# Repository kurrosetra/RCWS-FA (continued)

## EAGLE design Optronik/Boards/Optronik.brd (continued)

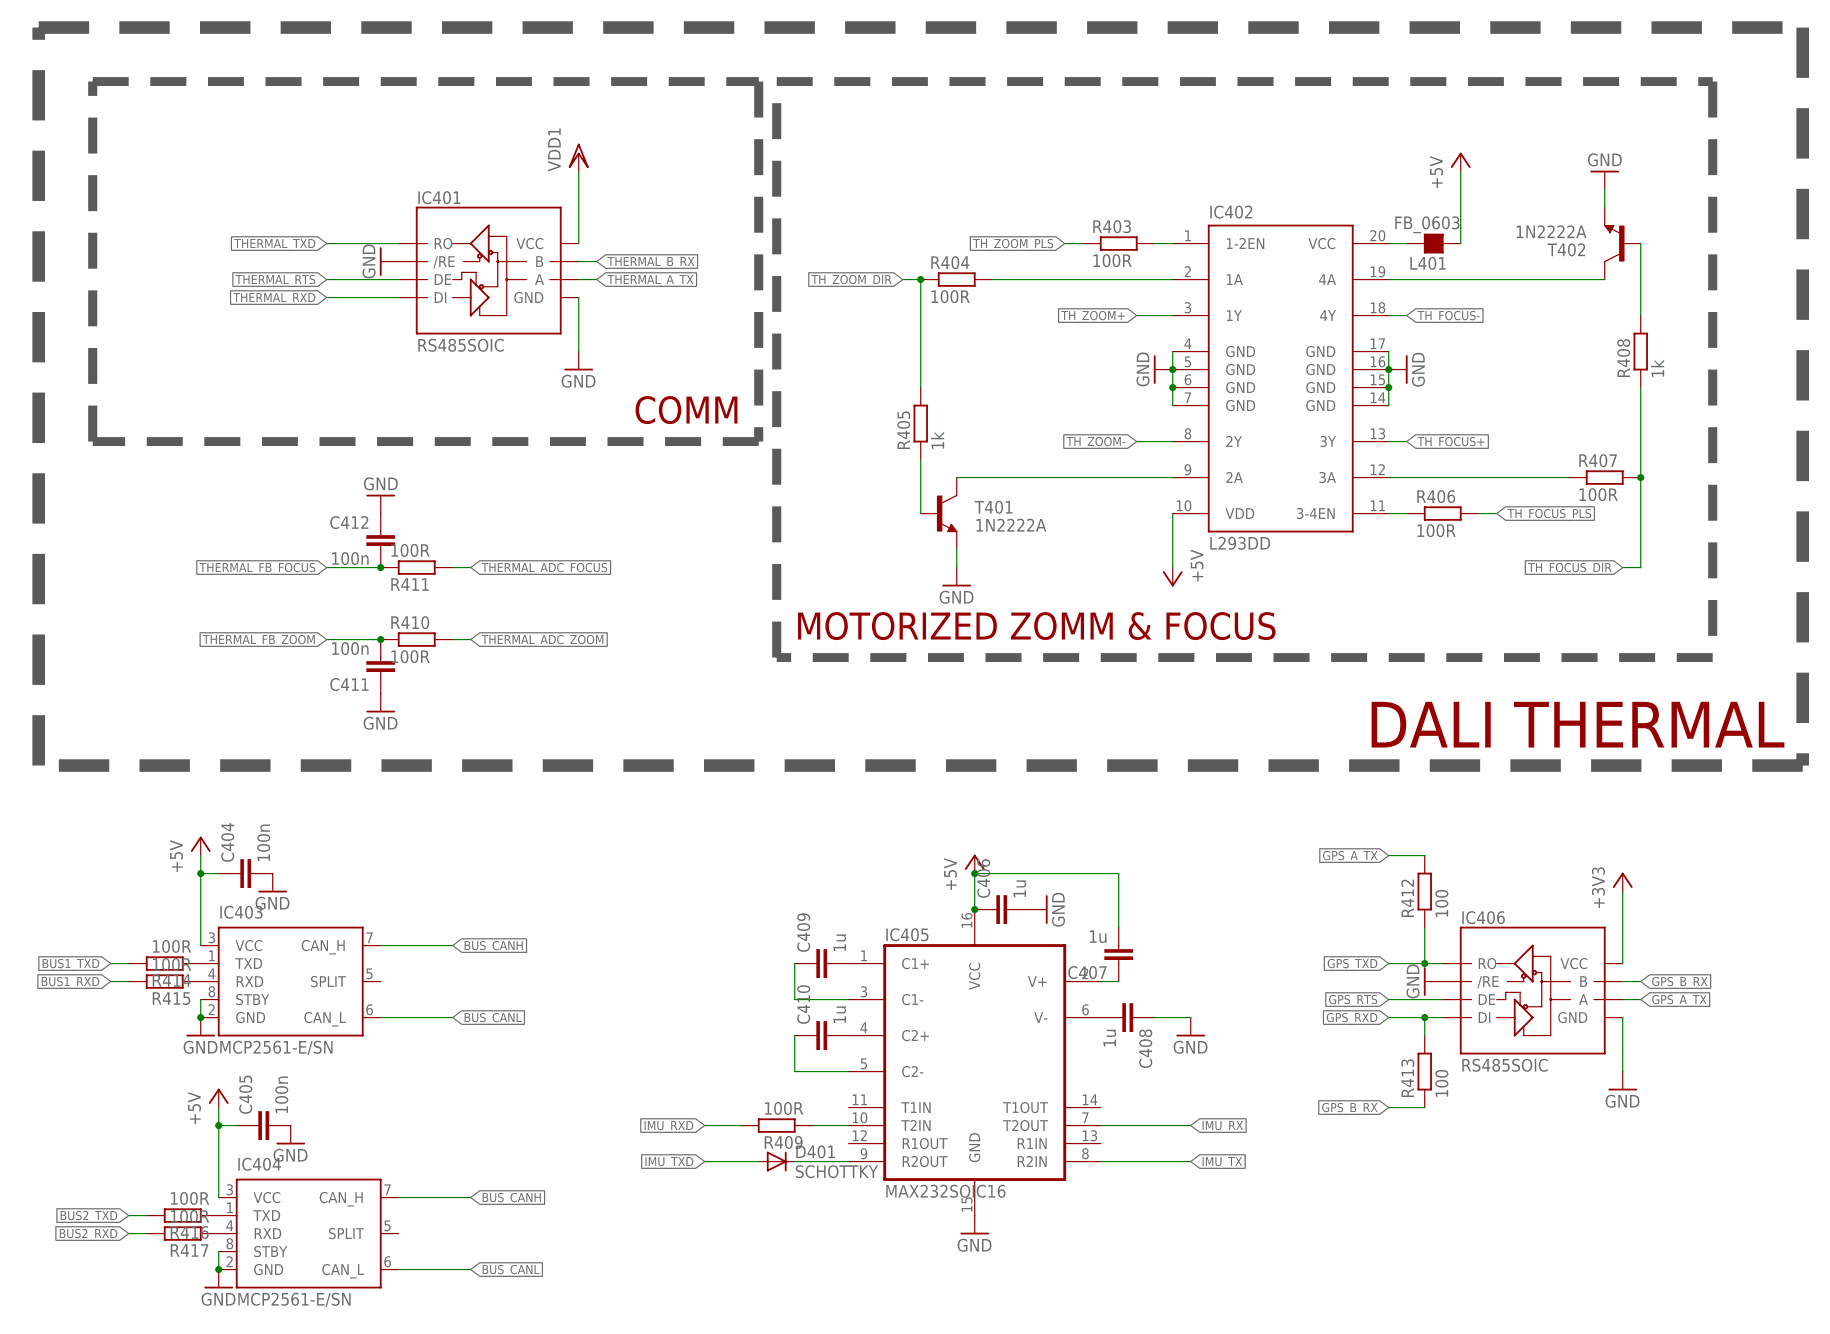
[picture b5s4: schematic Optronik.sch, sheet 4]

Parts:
C404, C405, C411, C412: 100n; C0603
C406, C407, C408, C409, C410: 1u; C0603
D401: SCHOTTKY; MICROMELF-W
IC401, IC406: RS485SOIC; SO08
IC402: L293DD; SO20W
IC403, IC404: MCP2561-E/SN; SOIC-8
IC405: MAX232SOIC16; SO016
L401: FB_0603; L0603
R403, R404, R406, R407, R409, R410, R411, R414, R415, R416, R417: 100R; R0603
R405, R408: 1k; R0603
R412, R413: 100; R0603
T401, T402: 1N2222A; SOT23

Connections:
+3V3: IC406.8 (VCC); also elsewhere on the board
+5V: C404.1, C405.1, C406.1, C407.2, IC402.10 (VDD), IC403.3 (VCC), IC404.3 (VCC), IC405.16 (VCC), L401.1; also elsewhere on the board
BUS1_RXD: R415.2; also elsewhere on the board
BUS1_TXD: R414.2; also elsewhere on the board
BUS2_RXD: R417.2; also elsewhere on the board
BUS2_TXD: R416.2; also elsewhere on the board
BUS_CANH: IC403.7 (CAN_H), IC404.7 (CAN_H); also elsewhere on the board
BUS_CANL: IC403.6 (CAN_L), IC404.6 (CAN_L); also elsewhere on the board
GND: C404.2, C405.2, C406.2, C408.1, C411.1, C412.1, IC401.2 (/RE), IC401.5 (GND), IC402.4 (GND), IC402.5 (GND), IC402.6 (GND), IC402.7 (GND), IC402.14 (GND), IC402.15 (GND), IC402.16 (GND), IC402.17 (GND), IC403.2 (GND), IC403.8 (STBY), IC404.2 (GND), IC404.8 (STBY), IC405.15 (GND), IC406.2 (/RE), IC406.5 (GND), T401.2 (E), T402.2 (E); also elsewhere on the board
GPS_A_TX: IC406.6 (A), R412.2; also elsewhere on the board
GPS_B_RX: IC406.7 (B), R413.1; also elsewhere on the board
GPS_RTS: IC406.3 (DE); also elsewhere on the board
GPS_RXD: IC406.4 (DI), R413.2; also elsewhere on the board
GPS_TXD: IC406.1 (RO), R412.1; also elsewhere on the board
IMU_RX: IC405.7 (T2OUT); also elsewhere on the board
IMU_RXD: R409.2; also elsewhere on the board
IMU_TX: IC405.8 (R2IN); also elsewhere on the board
IMU_TXD: D401.A; also elsewhere on the board
unnamed: IC402.20 (VCC), L401.2
unnamed: C408.2, IC405.6 (V-)
unnamed: C409.2, IC405.1 (C1+)
unnamed: C410.2, IC405.4 (C2+)
unnamed: IC402.12 (3A), R407.1
unnamed: IC403.1 (TXD), R414.1
unnamed: IC402.2 (1A), R404.2
unnamed: IC403.4 (RXD), R415.1
unnamed: C409.1, IC405.3 (C1-)
unnamed: C410.1, IC405.5 (C2-)
unnamed: IC404.1 (TXD), R416.1
unnamed: C407.1, IC405.2 (V+)
unnamed: IC404.4 (RXD), R417.1
unnamed: IC405.10 (T2IN), R409.1
unnamed: D401.C, IC405.9 (R2OUT)
unnamed: IC402.1 (1-2EN), R403.2
unnamed: IC402.11 (3-4EN), R406.1
unnamed: R405.1, T401.1 (B)
unnamed: IC402.9 (2A), T401.3 (C)
unnamed: IC402.19 (4A), T402.3 (C)
unnamed: R408.2, T402.1 (B)
THERMAL_ADC_FOCUS: R411.2; also elsewhere on the board
THERMAL_ADC_ZOOM: R410.2; also elsewhere on the board
THERMAL_A_TX: IC401.6 (A); also elsewhere on the board
THERMAL_B_RX: IC401.7 (B); also elsewhere on the board
THERMAL_FB_FOCUS: C412.2, R411.1; also elsewhere on the board
THERMAL_FB_ZOOM: C411.2, R410.1; also elsewhere on the board
THERMAL_RTS: IC401.3 (DE); also elsewhere on the board
THERMAL_RXD: IC401.4 (DI); also elsewhere on the board
THERMAL_TXD: IC401.1 (RO); also elsewhere on the board
TH_FOCUS+: IC402.13 (3Y); also elsewhere on the board
TH_FOCUS-: IC402.18 (4Y); also elsewhere on the board
TH_FOCUS_DIR: R407.2, R408.1; also elsewhere on the board
TH_FOCUS_PLS: R406.2; also elsewhere on the board
TH_ZOOM+: IC402.3 (1Y); also elsewhere on the board
TH_ZOOM-: IC402.8 (2Y); also elsewhere on the board
TH_ZOOM_DIR: R404.1, R405.2; also elsewhere on the board
TH_ZOOM_PLS: R403.1; also elsewhere on the board
VDD1: IC401.8 (VCC); also elsewhere on the board

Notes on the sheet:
DALI THERMAL
COMM
MOTORIZED ZOMM & FOCUS

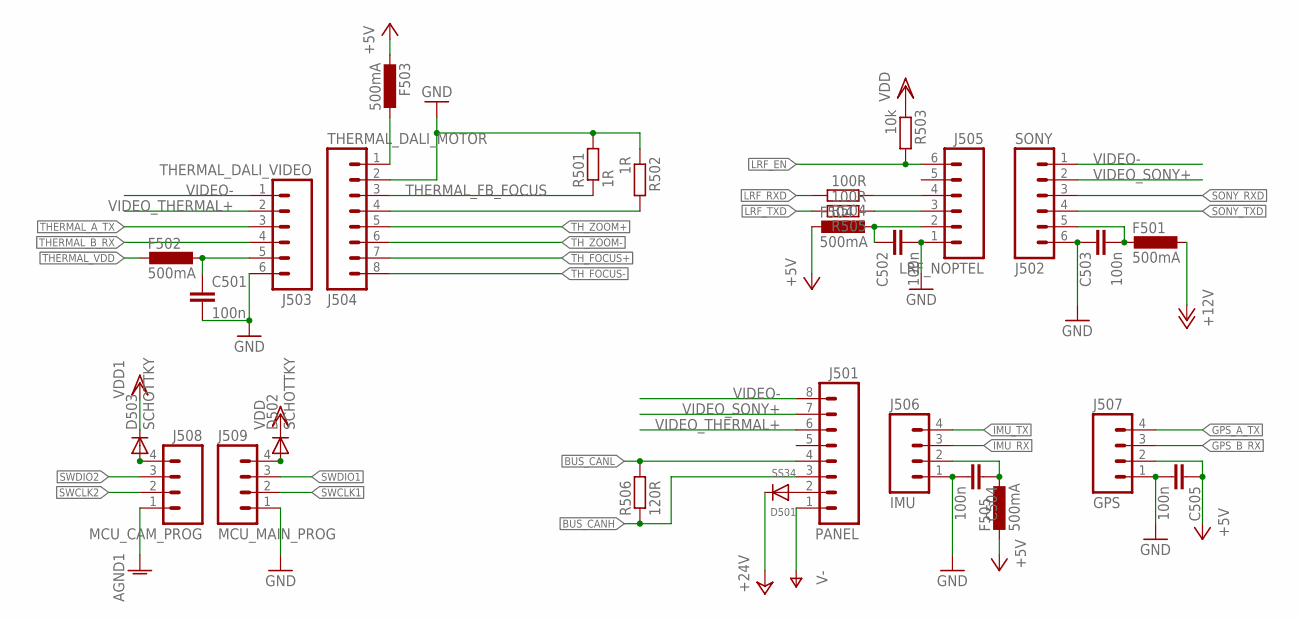
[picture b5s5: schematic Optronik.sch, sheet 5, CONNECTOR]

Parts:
C501, C502, C503, C504, C505: 100n; C0603
D501: SS34; SMADIODE
D502, D503: SCHOTTKY; MICROMELF-W
F501, F502, F503, F504, F505: 500mA; L0805
J501: PANEL; XH-8-RA
J502: SONY; XH-6-RA
J503: THERMAL_DALI_VIDEO; XH-6-RA
J504: THERMAL_DALI_MOTOR; XH-8-RA
J505: LRF_NOPTEL; XH-6-RA
J506: IMU; XH-4-RA
J507: GPS; XH-4-RA
J508: MCU_CAM_PROG; XH-4-VERT
J509: MCU_MAIN_PROG; XH-4-VERT
R501, R502: 1R; 0411V
R503: 10k; R0603
R504, R505: 100R; R0603
R506: 120R; R0603

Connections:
+5V: C505.1, F503.2, F504.2, F505.2, J507.2; also elsewhere on the board
+12V: F501.1; also elsewhere on the board
+24V: D501.C; also elsewhere on the board
AGND1: J508.1; also elsewhere on the board
BUS_CANH: J501.3, R506.1; also elsewhere on the board
BUS_CANL: J501.4, R506.2; also elsewhere on the board
GND: C501.2, C502.2, C503.1, C504.2, C505.2, J502.6, J503.6, J504.2, J505.1, J506.1, J507.1, J509.1, R501.2, R502.1; also elsewhere on the board
GPS_A_TX: J507.4; also elsewhere on the board
GPS_B_RX: J507.3; also elsewhere on the board
IMU_RX: J506.3; also elsewhere on the board
IMU_TX: J506.4; also elsewhere on the board
LRF_EN: J505.6, R503.2; also elsewhere on the board
LRF_RXD: R504.2; also elsewhere on the board
LRF_TXD: R505.2; also elsewhere on the board
unnamed: D501.A, J501.2
unnamed: F503.1, J504.1
unnamed: D502.A, J509.4
unnamed: C501.1, F502.1, J503.5
unnamed: C502.1, F504.1, J505.2
unnamed: C503.2, F501.2, J502.5
unnamed: C504.1, F505.1, J506.2
unnamed: J505.3, R505.1
unnamed: J505.4, R504.1
unnamed: D503.A, J508.4
SONY_RXD: J502.3; also elsewhere on the board
SONY_TXD: J502.4; also elsewhere on the board
SWCLK1: J509.2; also elsewhere on the board
SWCLK2: J508.2; also elsewhere on the board
SWDIO1: J509.3; also elsewhere on the board
SWDIO2: J508.3; also elsewhere on the board
THERMAL_A_TX: J503.3; also elsewhere on the board
THERMAL_B_RX: J503.4; also elsewhere on the board
THERMAL_FB_FOCUS: J504.3, R501.1; also elsewhere on the board
THERMAL_FB_ZOOM: J504.4, R502.2; also elsewhere on the board
THERMAL_VDD: F502.2; also elsewhere on the board
TH_FOCUS+: J504.7; also elsewhere on the board
TH_FOCUS-: J504.8; also elsewhere on the board
TH_ZOOM+: J504.5; also elsewhere on the board
TH_ZOOM-: J504.6; also elsewhere on the board
V-: J501.1; also elsewhere on the board
VDD: D502.C, R503.1; also elsewhere on the board
VDD1: D503.C; also elsewhere on the board
VIDEO-: J501.8, J502.1, J503.1
VIDEO_SONY+: J501.7, J502.2
VIDEO_THERMAL+: J501.6, J503.2

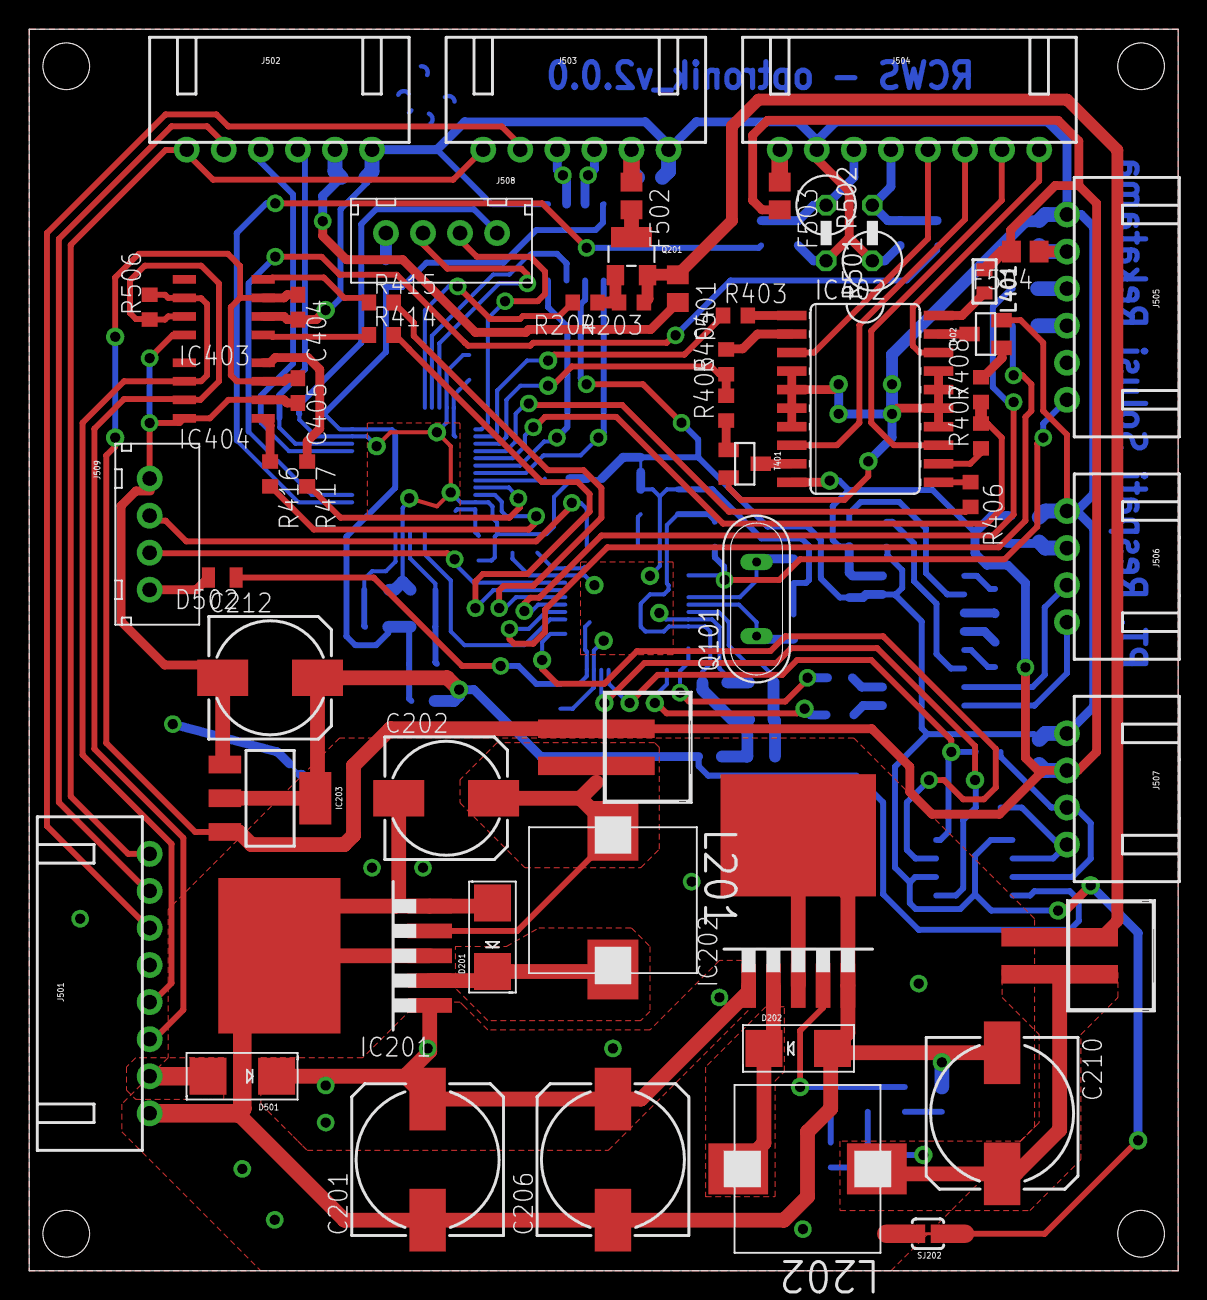
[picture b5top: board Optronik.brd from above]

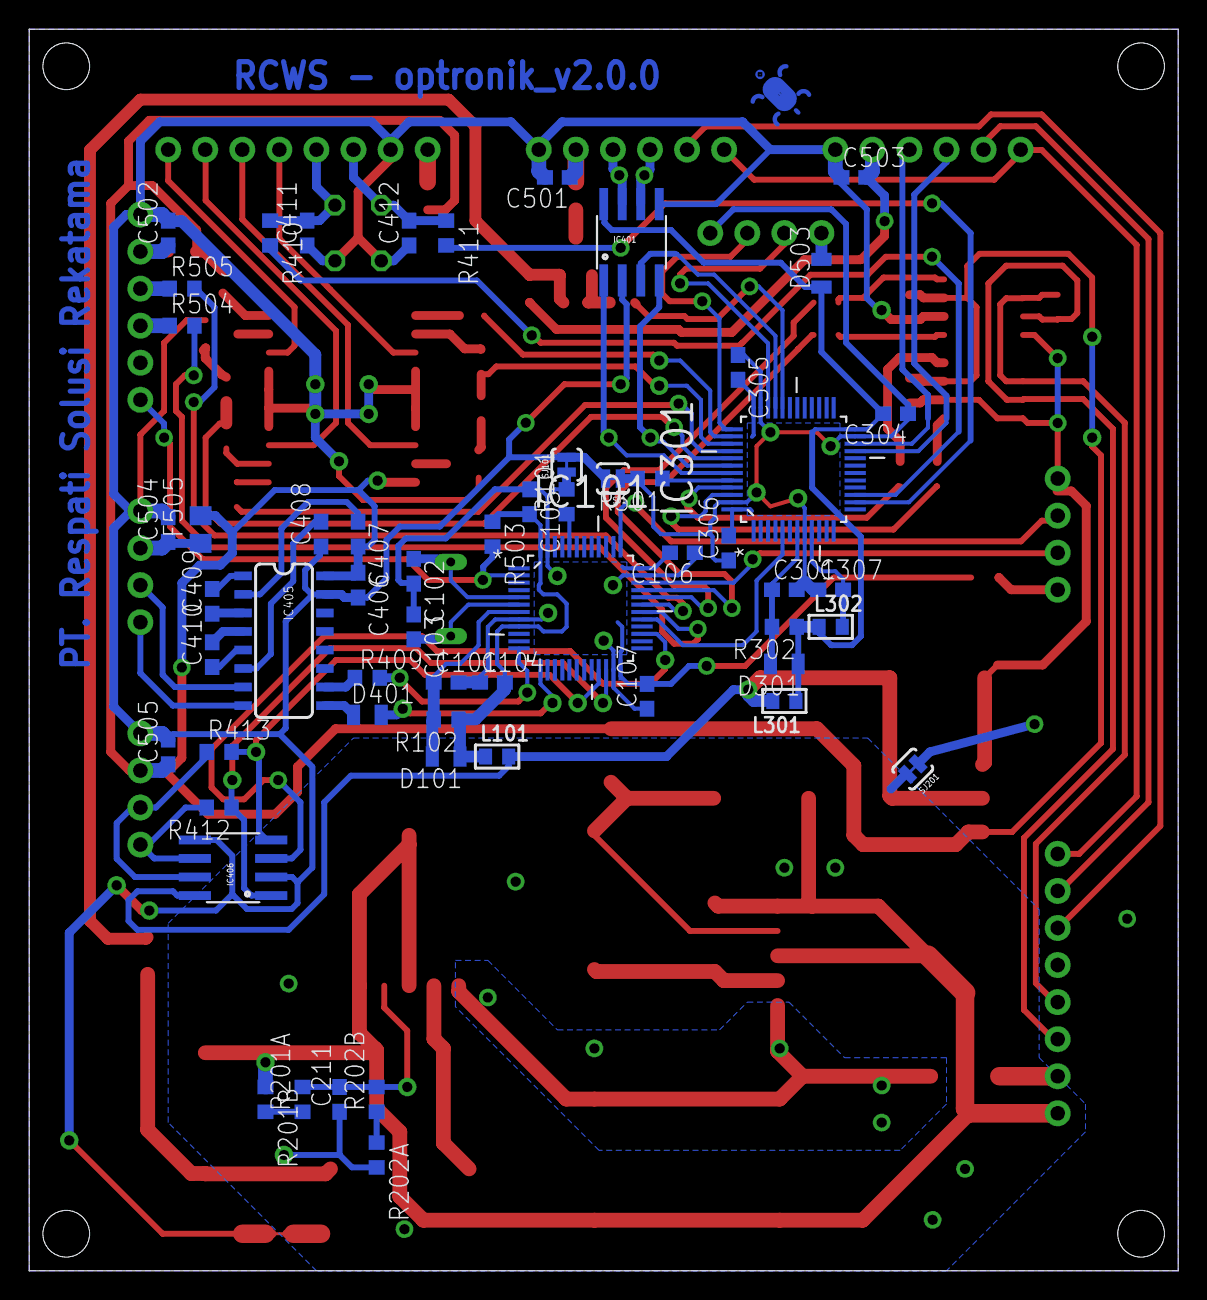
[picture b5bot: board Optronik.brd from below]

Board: 2 copper layers, 78.7 x 85.1 mm, 113 parts (57 on the bottom side), 103 nets.

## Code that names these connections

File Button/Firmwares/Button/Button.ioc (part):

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Mcu.Name=STM32F103C(8-B)Tx
Mcu.Package=LQFP48
Mcu.UserName=STM32F103C8Tx
PA0-WKUP.GPIOParameters=GPIO_PuPd,GPIO_Label
PA0-WKUP.GPIO_Label=TRK_ON
PA0-WKUP.GPIO_PuPd=GPIO_PULLUP
PA0-WKUP.Signal=GPIO_Input
PA1.GPIOParameters=GPIO_PuPd,GPIO_Label
PA1.GPIO_Label=FIRE_ACTIVE
PA1.GPIO_PuPd=GPIO_PULLUP
PA1.Signal=GPIO_Input
PA10.GPIOParameters=GPIO_PuPd,GPIO_Label
PA10.GPIO_Label=PANEL_TXD
PA10.GPIO_PuPd=GPIO_PULLUP
PA10.Mode=Asynchronous
PA10.Signal=USART1_RX
PA11.Signal=CAN_RX
PA12.Signal=CAN_TX
PA13.Mode=Serial_Wire
PA13.Signal=SYS_JTMS-SWDIO
PA14.Mode=Serial_Wire
PA14.Signal=SYS_JTCK-SWCLK
PA15.GPIOParameters=GPIO_PuPd,GPIO_Label,GPIO_Mode
PA15.GPIO_Label=CAM_ZOOM_OUT
PA15.GPIO_Mode=GPIO_MODE_INPUT
PA15.GPIO_PuPd=GPIO_PULLUP
PA15.Signal=GPIO_Input
PA2.GPIOParameters=GPIO_PuPd,GPIO_Label,GPIO_Mode
PA2.GPIO_Label=TRK_PREV
PA2.GPIO_Mode=GPIO_MODE_INPUT
PA2.GPIO_PuPd=GPIO_PULLUP
PA2.Signal=GPIO_Input
PA3.GPIOParameters=GPIO_PuPd,GPIO_Label,GPIO_Mode
PA3.GPIO_Label=CAM_FOCUS_NEAR
PA3.GPIO_Mode=GPIO_MODE_INPUT
PA3.GPIO_PuPd=GPIO_PULLUP
PA3.Signal=GPIO_Input
PA4.GPIOParameters=GPIO_PuPd,GPIO_Label,GPIO_Mode
PA4.GPIO_Label=CAM_SEL_THERMAL
PA4.GPIO_Mode=GPIO_MODE_INPUT
PA4.GPIO_PuPd=GPIO_PULLUP
PA4.Signal=GPIO_Input
PA5.GPIOParameters=GPIO_Label
PA5.GPIO_Label=JSL_ELEVATION
PA5.Signal=ADCx_IN5
PA6.GPIOParameters=GPIO_Label
PA6.GPIO_Label=JSL_AZIMUTH
PA6.Signal=ADCx_IN6
PA7.GPIOParameters=GPIO_PuPd,GPIO_Label,GPIO_Mode
PA7.GPIO_Label=JSR_DEADMAN
PA7.GPIO_Mode=GPIO_MODE_INPUT
PA7.GPIO_PuPd=GPIO_PULLUP
PA7.Signal=GPIO_Input
PA8.GPIOParameters=GPIO_PuPd,GPIO_Label,GPIO_Mode
PA8.GPIO_Label=JSL_TRIG
PA8.GPIO_Mode=GPIO_MODE_INPUT
PA8.GPIO_PuPd=GPIO_PULLUP
PA8.Signal=GPIO_Input
PA9.GPIOParameters=GPIO_Label
PA9.GPIO_Label=PANEL_RXD
PA9.Mode=Asynchronous
PA9.Signal=USART1_TX
PB0.GPIOParameters=GPIO_Label
PB0.GPIO_Label=JSR_AZIMUTH
PB0.Signal=ADCx_IN8
PB1.GPIOParameters=GPIO_Label
PB1.GPIO_Label=JSR_ELEVATION
PB1.Signal=ADCx_IN9
PB10.GPIOParameters=GPIO_PuPd,GPIO_Label,GPIO_Mode
PB10.GPIO_Label=JSR_B
PB10.GPIO_Mode=GPIO_MODE_INPUT
PB10.GPIO_PuPd=GPIO_PULLUP
PB10.Signal=GPIO_Input
PB11.GPIOParameters=GPIO_PuPd,GPIO_Label,GPIO_Mode
PB11.GPIO_Label=JSR_TRIG
PB11.GPIO_Mode=GPIO_MODE_INPUT
PB11.GPIO_PuPd=GPIO_PULLUP
PB11.Signal=GPIO_Input
PB12.GPIOParameters=PinState,GPIO_Label
PB12.GPIO_Label=LED
PB12.PinState=GPIO_PIN_SET
PB12.Signal=GPIO_Output
PB13.GPIOParameters=GPIO_PuPd,GPIO_Label,GPIO_Mode
PB13.GPIO_Label=JSL_DEADMAN
PB13.GPIO_Mode=GPIO_MODE_INPUT
PB13.GPIO_PuPd=GPIO_PULLUP
PB13.Signal=GPIO_Input
PB14.GPIOParameters=GPIO_PuPd,GPIO_Label,GPIO_Mode
PB14.GPIO_Label=JSL_A
PB14.GPIO_Mode=GPIO_MODE_INPUT
PB14.GPIO_PuPd=GPIO_PULLUP
PB14.Signal=GPIO_Input
PB15.GPIOParameters=GPIO_PuPd,GPIO_Label,GPIO_Mode
PB15.GPIO_Label=JSL_B
PB15.GPIO_Mode=GPIO_MODE_INPUT
PB15.GPIO_PuPd=GPIO_PULLUP
PB15.Signal=GPIO_Input
PB2.GPIOParameters=GPIO_PuPd,GPIO_Label,GPIO_Mode
PB2.GPIO_Label=JSR_A
PB2.GPIO_Mode=GPIO_MODE_INPUT
PB2.GPIO_PuPd=GPIO_PULLUP
PB2.Signal=GPIO_Input
PB3.GPIOParameters=GPIO_PuPd,GPIO_Label,GPIO_Mode
PB3.GPIO_Label=LRF_MAN_DOWN
PB3.GPIO_Mode=GPIO_MODE_INPUT
PB3.GPIO_PuPd=GPIO_PULLUP
PB3.Signal=GPIO_Input
PB4.GPIOParameters=GPIO_PuPd,GPIO_Label,GPIO_Mode
PB4.GPIO_Label=LRF_START
PB4.GPIO_Mode=GPIO_MODE_INPUT
PB4.GPIO_PuPd=GPIO_PULLUP
PB4.Signal=GPIO_Input
PB5.GPIOParameters=GPIO_PuPd,GPIO_Label,GPIO_Mode
PB5.GPIO_Label=MTR_SPD_HIGH
PB5.GPIO_Mode=GPIO_MODE_INPUT
PB5.GPIO_PuPd=GPIO_PULLUP
PB5.Signal=GPIO_Input
PB6.GPIOParameters=GPIO_PuPd,GPIO_Label,GPIO_Mode
PB6.GPIO_Label=MTR_SPD_LOW
PB6.GPIO_Mode=GPIO_MODE_INPUT
PB6.GPIO_PuPd=GPIO_PULLUP
PB6.Signal=GPIO_Input
PB7.GPIOParameters=GPIO_PuPd,GPIO_Label,GPIO_Mode
PB7.GPIO_Label=LRF_EN
PB7.GPIO_Mode=GPIO_MODE_INPUT
PB7.GPIO_PuPd=GPIO_PULLUP
PB7.Signal=GPIO_Input
PB8.GPIOParameters=GPIO_PuPd,GPIO_Label,GPIO_Mode
PB8.GPIO_Label=LRF_MAN_UP
PB8.GPIO_Mode=GPIO_MODE_INPUT
PB8.GPIO_PuPd=GPIO_PULLUP
PB8.Signal=GPIO_Input
PB9.GPIOParameters=GPIO_PuPd,GPIO_Label,GPIO_Mode
PB9.GPIO_Label=CAM_ZOOM_IN
PB9.GPIO_Mode=GPIO_MODE_INPUT
PB9.GPIO_PuPd=GPIO_PULLUP
PB9.Signal=GPIO_Input
PC13-TAMPER-RTC.GPIOParameters=GPIO_Label
PC13-TAMPER-RTC.GPIO_Label=LED1
PC13-TAMPER-RTC.Signal=GPIO_Output
PC14-OSC32_IN.GPIOParameters=GPIO_Label
PC14-OSC32_IN.GPIO_Label=LED2
PC14-OSC32_IN.Signal=GPIO_Output
PC15-OSC32_OUT.GPIOParameters=GPIO_PuPd,GPIO_Label,GPIO_Mode
PC15-OSC32_OUT.GPIO_Label=CAM_SEL_DAY
PC15-OSC32_OUT.GPIO_Mode=GPIO_MODE_INPUT
PC15-OSC32_OUT.GPIO_PuPd=GPIO_PULLUP
PC15-OSC32_OUT.Signal=GPIO_Input
PD0-OSC_IN.GPIOParameters=GPIO_PuPd,GPIO_Label,GPIO_Mode
PD0-OSC_IN.GPIO_Label=CAM_FOCUS_FAR
PD0-OSC_IN.GPIO_Mode=GPIO_MODE_INPUT
PD0-OSC_IN.GPIO_PuPd=GPIO_PULLUP
PD0-OSC_IN.Signal=GPIO_Input
PD1-OSC_OUT.GPIOParameters=GPIO_PuPd,GPIO_Label,GPIO_Mode
PD1-OSC_OUT.GPIO_Label=TRK_NEXT
PD1-OSC_OUT.GPIO_Mode=GPIO_MODE_INPUT
PD1-OSC_OUT.GPIO_PuPd=GPIO_PULLUP
PD1-OSC_OUT.Signal=GPIO_Input
RCC.SYSCLKFreq_VALUE=36000000
RCC.SYSCLKSource=RCC_SYSCLKSOURCE_PLLCLK
board=custom

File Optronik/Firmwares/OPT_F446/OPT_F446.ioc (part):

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Mcu.Name=STM32F446R(C-E)Tx
Mcu.Package=LQFP64
Mcu.UserName=STM32F446RETx
PA0-WKUP.GPIOParameters=GPIO_Label
PA0-WKUP.GPIO_Label=DEBUG_RXD
PA0-WKUP.Mode=Asynchronous
PA0-WKUP.Signal=UART4_TX
PA1.GPIOParameters=GPIO_Label
PA1.GPIO_Label=DEBUG_TXD
PA1.Mode=Asynchronous
PA1.Signal=UART4_RX
PA10.GPIOParameters=GPIO_Label
PA10.GPIO_Label=RESV_TXD
PA10.Signal=USART1_RX
PA11.Mode=CAN_Activate
PA11.Signal=CAN1_RX
PA12.Mode=CAN_Activate
PA12.Signal=CAN1_TX
PA13.GPIOParameters=GPIO_Label
PA13.GPIO_Label=TMS
PA13.Mode=Serial_Wire
PA13.Signal=SYS_JTMS-SWDIO
PA14.GPIOParameters=GPIO_Label
PA14.GPIO_Label=TCK
PA14.Mode=Serial_Wire
PA14.Signal=SYS_JTCK-SWCLK
PA15.GPIOParameters=GPIO_PuPd,GPIO_Label
PA15.GPIO_Label=THERMAL_PWR_EN
PA15.GPIO_PuPd=GPIO_PULLUP
PA15.Signal=GPIO_Output
PA2.GPIOParameters=GPIO_Label
PA2.GPIO_Label=LRF_RXD
PA2.Mode=Asynchronous
PA2.Signal=USART2_TX
PA3.GPIOParameters=GPIO_Label
PA3.GPIO_Label=LRF_TXD
PA3.Mode=Asynchronous
PA3.Signal=USART2_RX
PA4.Signal=GPIO_Input
PA5.Signal=GPIO_Input
PA6.GPIOParameters=GPIO_Speed,PinState,GPIO_PuPd,GPIO_Label
PA6.GPIO_Label=LRF_EN
PA6.GPIO_PuPd=GPIO_PULLUP
PA6.GPIO_Speed=GPIO_SPEED_FREQ_VERY_HIGH
PA6.PinState=GPIO_PIN_SET
PA6.Signal=GPIO_Output
PA7.Signal=GPIO_Input
PA9.GPIOParameters=GPIO_Label
PA9.GPIO_Label=RESV_RXD
PA9.Signal=USART1_TX
PB15.GPIOParameters=GPIO_PuPd,GPIO_Label
PB15.GPIO_Label=CAM_SELECT
PB15.GPIO_PuPd=GPIO_PULLUP
PB15.Signal=GPIO_Output
PB3.GPIOParameters=GPIO_Speed,GPIO_PuPd,GPIO_Label
PB3.GPIO_Label=THERMAL_DE
PB3.GPIO_PuPd=GPIO_PULLUP
PB3.GPIO_Speed=GPIO_SPEED_FREQ_VERY_HIGH
PB3.Signal=GPIO_Output
PB6.GPIOParameters=PinState,GPIO_PuPd,GPIO_Label
PB6.GPIO_Label=LED_BUILTIN
PB6.GPIO_PuPd=GPIO_PULLUP
PB6.PinState=GPIO_PIN_SET
PB6.Signal=GPIO_Output
PC10.GPIOParameters=GPIO_Label
PC10.GPIO_Label=THERMAL_RXD
PC10.Mode=Asynchronous
PC10.Signal=USART3_TX
PC11.GPIOParameters=GPIO_Label
PC11.GPIO_Label=THERMAL_TXD
PC11.Mode=Asynchronous
PC11.Signal=USART3_RX
PC12.GPIOParameters=GPIO_Label
PC12.GPIO_Label=IMU_RXD
PC12.Signal=UART5_TX
PC4.Signal=GPIO_Input
PC6.GPIOParameters=GPIO_Label
PC6.GPIO_Label=SONY_RXD
PC6.Mode=Asynchronous
PC6.Signal=USART6_TX
PC7.GPIOParameters=GPIO_Label
PC7.GPIO_Label=SONY_TXD
PC7.Mode=Asynchronous
PC7.Signal=USART6_RX
PD2.GPIOParameters=GPIO_Label
PD2.GPIO_Label=IMU_TXD
PD2.Signal=UART5_RX
PH0-OSC_IN.Mode=HSE-External-Oscillator
PH0-OSC_IN.Signal=RCC_OSC_IN
PH1-OSC_OUT.Mode=HSE-External-Oscillator
PH1-OSC_OUT.Signal=RCC_OSC_OUT
RCC.HSE_VALUE=8000000
RCC.SYSCLKFreq_VALUE=180000000
RCC.SYSCLKSource=RCC_SYSCLKSOURCE_PLLCLK
board=NUCLEO-F446RE
boardIOC=true

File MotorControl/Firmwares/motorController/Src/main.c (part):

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#endif	//if DEBUG==1

	if (motorInit() != HAL_OK) {
		HAL_GPIO_WritePin(LED_BUILTIN_GPIO_Port, LED_BUILTIN_Pin, GPIO_PIN_RESET);
		while (1)
			;
	}
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#endif	//if DEBUG==1

	if (busInit() != HAL_OK) {
		HAL_GPIO_WritePin(LED_BUILTIN_GPIO_Port, LED_BUILTIN_Pin, GPIO_PIN_RESET);
		while (1)
			;
	}
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	;

	/*Configure GPIO pin Output Level */
	HAL_GPIO_WritePin(LED_BUILTIN_GPIO_Port, LED_BUILTIN_Pin, GPIO_PIN_SET);

	/*Configure GPIO pin Output Level */
	HAL_GPIO_WritePin(TRIGGER_ENABLE_GPIO_Port, TRIGGER_ENABLE_Pin, GPIO_PIN_RESET);

	/*Configure GPIO pins : PC13 PC14 PC15 PC0
	 PC1 PC2 PC3 PC4
	 PC5 PC8 PC9 PC10
	 PC11 PC12 */
	GPIO_InitStruct.Pin = GPIO_PIN_13 | GPIO_PIN_14 | GPIO_PIN_15 | GPIO_PIN_0 | GPIO_PIN_1
			| GPIO_PIN_2 | GPIO_PIN_3 | GPIO_PIN_4 | GPIO_PIN_5 | GPIO_PIN_8 | GPIO_PIN_9
			| GPIO_PIN_10 | GPIO_PIN_11 | GPIO_PIN_12;
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	GPIO_InitStruct.Pull = GPIO_NOPULL;
	HAL_GPIO_Init(GPIOC, &GPIO_InitStruct);

	/*Configure GPIO pins : PA0 PA4 PA5 PA6
	 PA8 PA9 PA10 PA11
	 PA12 PA15 */
	GPIO_InitStruct.Pin = GPIO_PIN_0 | GPIO_PIN_4 | GPIO_PIN_5 | GPIO_PIN_6 | GPIO_PIN_8
			| GPIO_PIN_9 | GPIO_PIN_10 | GPIO_PIN_11 | GPIO_PIN_12 | GPIO_PIN_15;
	GPIO_InitStruct.Mode = GPIO_MODE_ANALOG;
	GPIO_InitStruct.Pull = GPIO_NOPULL;
	HAL_GPIO_Init(GPIOA, &GPIO_InitStruct);

	/*Configure GPIO pins : LIM_AZ_Pin LIM_EL_UP_Pin LIM_EL_DOWN_Pin */
	GPIO_InitStruct.Pin = LIM_AZ_Pin | LIM_EL_UP_Pin | LIM_EL_DOWN_Pin;
	GPIO_InitStruct.Mode = GPIO_MODE_IT_FALLING;
	GPIO_InitStruct.Pull = GPIO_PULLUP;
	HAL_GPIO_Init(GPIOA, &GPIO_InitStruct);

	/*Configure GPIO pin : LED_BUILTIN_Pin */
	GPIO_InitStruct.Pin = LED_BUILTIN_Pin;
	GPIO_InitStruct.Mode = GPIO_MODE_OUTPUT_PP;
	GPIO_InitStruct.Pull = GPIO_NOPULL;
	GPIO_InitStruct.Speed = GPIO_SPEED_FREQ_HIGH;
	HAL_GPIO_Init(LED_BUILTIN_GPIO_Port, &GPIO_InitStruct);

	/*Configure GPIO pins : PB0 PB1 PB2 PB10
	 PB14 PB15 PB3 PB5
	 PB6 PB7 */
	GPIO_InitStruct.Pin = GPIO_PIN_0 | GPIO_PIN_1 | GPIO_PIN_2 | GPIO_PIN_10 | GPIO_PIN_14
			| GPIO_PIN_15 | GPIO_PIN_3 | GPIO_PIN_5 | GPIO_PIN_6 | GPIO_PIN_7;
	GPIO_InitStruct.Mode = GPIO_MODE_ANALOG;
	GPIO_InitStruct.Pull = GPIO_NOPULL;
	HAL_GPIO_Init(GPIOB, &GPIO_InitStruct);

	/*Configure GPIO pin : PD2 */
	GPIO_InitStruct.Pin = GPIO_PIN_2;
	GPIO_InitStruct.Mode = GPIO_MODE_ANALOG;
	GPIO_InitStruct.Pull = GPIO_NOPULL;
	HAL_GPIO_Init(GPIOD, &GPIO_InitStruct);

	/*Configure GPIO pin : TRIGGER_ENABLE_Pin */
	GPIO_InitStruct.Pin = TRIGGER_ENABLE_Pin;
	GPIO_InitStruct.Mode = GPIO_MODE_OUTPUT_PP;
	GPIO_InitStruct.Pull = GPIO_PULLDOWN;
	GPIO_InitStruct.Speed = GPIO_SPEED_FREQ_HIGH;
	HAL_GPIO_Init(TRIGGER_ENABLE_GPIO_Port, &GPIO_InitStruct);

}

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
	/* check TRIGGER command */
	if (HAL_GetTick() >= buttonCommandTimeout) {
		HAL_GPIO_WritePin(TRIGGER_ENABLE_GPIO_Port, TRIGGER_ENABLE_Pin, GPIO_PIN_RESET);
		canRecvButton.online = false;
	}

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		buttonCommandTimeout = HAL_GetTick() + COMMAND_RECEIVE_TIMEOUT;
		canRecvButton.online = true;

		HAL_GPIO_WritePin(TRIGGER_ENABLE_GPIO_Port, TRIGGER_ENABLE_Pin,
				bitRead(canRecvButton.data[0], 0));

		cockStart = bitRead(canRecvButton.data[0], 1);
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	if (canRecvMoveMode.online) {
		/* check movement mode command (from panel) */
		if (HAL_GetTick() >= movementModeTimeout) {
			HAL_GPIO_WritePin(LED_BUILTIN_GPIO_Port, LED_BUILTIN_Pin, GPIO_PIN_RESET);
			canRecvMoveMode.online = false;
		}

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			initMovementState();
		}

		HAL_GPIO_TogglePin(LED_BUILTIN_GPIO_Port, LED_BUILTIN_Pin);
	}

}
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		_stateTimer = HAL_GetTick() + 100;

		bitWrite(canSendMotor.data[1], 0,
				HAL_GPIO_ReadPin(TRIGGER_ENABLE_GPIO_Port, TRIGGER_ENABLE_Pin));
		bitWrite(canSendMotor.data[1], 1, cockStart);

		busTxHeader->StdId = canSendMotor.id;
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
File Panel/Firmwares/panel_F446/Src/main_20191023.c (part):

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typedef enum
{
	MTR_SPD_MID = 2,
	MTR_SPD_LOW = 0,
	MTR_SPD_HIGH = 3
} MotorSpeed_e;

const uint32_t MTR_PAN_SPEED_JOYSTICK_MAX = 100000;
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	HAL_IWDG_Init(&hiwdg);
	HAL_IWDG_Refresh(&hiwdg);

	HAL_GPIO_WritePin(LED_BUILTIN_GPIO_Port, LED_BUILTIN_Pin, GPIO_PIN_SET);

#if DEBUG
	serial_init(&debug);
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
			bufLen = sprintf(buf, "%sBattVolt= %dmV", vt100_lineX[2], battVoltActual(battVolt));
			serial_write_str(&debug, buf, bufLen);
			HAL_GPIO_TogglePin(LED_BUILTIN_GPIO_Port, LED_BUILTIN_Pin);
		}
#endif	//if DEBUG==1

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 * EXTI
 * Free pins are configured automatically as Analog (this feature is enabled through
 * the Code Generation settings)
 PC6   ------> USART6_TX
 PC7   ------> USART6_RX
 PC10   ------> UART4_TX
 PC11   ------> UART4_RX
 */
static void MX_GPIO_Init(void)
{
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	;

	/*Configure GPIO pin Output Level */
	HAL_GPIO_WritePin(GPIOC, PC_IGNITION_Pin | WIFI_RST_Pin, GPIO_PIN_RESET);

	/*Configure GPIO pin Output Level */
	HAL_GPIO_WritePin(WIFI_EN_GPIO_Port, WIFI_EN_Pin, GPIO_PIN_RESET);

	/*Configure GPIO pin Output Level */
	HAL_GPIO_WritePin(LED_BUILTIN_GPIO_Port, LED_BUILTIN_Pin, GPIO_PIN_RESET);

	/*Configure GPIO pins : PC13 PC14 PC15 PC0
	 PC1 PC2 PC3 PC4 */
	GPIO_InitStruct.Pin = GPIO_PIN_13 | GPIO_PIN_14 | GPIO_PIN_15 | GPIO_PIN_0 | GPIO_PIN_1
			| GPIO_PIN_2 | GPIO_PIN_3 | GPIO_PIN_4;
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	GPIO_InitStruct.Pull = GPIO_NOPULL;
	HAL_GPIO_Init(GPIOC, &GPIO_InitStruct);

	/*Configure GPIO pins : PA0 PA1 PA4 PA5
	 PA6 PA8 */
	GPIO_InitStruct.Pin = GPIO_PIN_0 | GPIO_PIN_1 | GPIO_PIN_4 | GPIO_PIN_5 | GPIO_PIN_6
			| GPIO_PIN_8;
	GPIO_InitStruct.Mode = GPIO_MODE_ANALOG;
	GPIO_InitStruct.Pull = GPIO_NOPULL;
	HAL_GPIO_Init(GPIOA, &GPIO_InitStruct);

	/*Configure GPIO pins : PB0 PB1 PB2 PB13
	 PB14 PB3 PB4 PB5
	 PB6 PB7 PB8 PB9 */
	GPIO_InitStruct.Pin = GPIO_PIN_0 | GPIO_PIN_1 | GPIO_PIN_2 | GPIO_PIN_13 | GPIO_PIN_14
			| GPIO_PIN_3 | GPIO_PIN_4 | GPIO_PIN_5 | GPIO_PIN_6 | GPIO_PIN_7 | GPIO_PIN_8
			| GPIO_PIN_9;
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	GPIO_InitStruct.Pull = GPIO_NOPULL;
	HAL_GPIO_Init(GPIOB, &GPIO_InitStruct);

	/*Configure GPIO pin : TRIGGER_IN_Pin */
	GPIO_InitStruct.Pin = TRIGGER_IN_Pin;
	GPIO_InitStruct.Mode = GPIO_MODE_INPUT;
	GPIO_InitStruct.Pull = GPIO_PULLUP;
	HAL_GPIO_Init(TRIGGER_IN_GPIO_Port, &GPIO_InitStruct);

	/*Configure GPIO pins : GPS_TX_Pin GPS_RX_Pin */
	GPIO_InitStruct.Pin = GPS_TX_Pin | GPS_RX_Pin;
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	GPIO_InitStruct.Alternate = GPIO_AF8_USART6;
	HAL_GPIO_Init(GPIOC, &GPIO_InitStruct);

	/*Configure GPIO pin : PC_PWR_CHECK_IN_Pin */
	GPIO_InitStruct.Pin = PC_PWR_CHECK_IN_Pin;
	GPIO_InitStruct.Mode = GPIO_MODE_INPUT;
	GPIO_InitStruct.Pull = GPIO_PULLUP;
	HAL_GPIO_Init(PC_PWR_CHECK_IN_GPIO_Port, &GPIO_InitStruct);

	/*Configure GPIO pin : PC_IGNITION_Pin */
	GPIO_InitStruct.Pin = PC_IGNITION_Pin;
	GPIO_InitStruct.Mode = GPIO_MODE_OUTPUT_PP;
	GPIO_InitStruct.Pull = GPIO_PULLDOWN;
	GPIO_InitStruct.Speed = GPIO_SPEED_FREQ_LOW;
	HAL_GPIO_Init(PC_IGNITION_GPIO_Port, &GPIO_InitStruct);

	/*Configure GPIO pin : WIFI_EN_Pin */
	GPIO_InitStruct.Pin = WIFI_EN_Pin;
	GPIO_InitStruct.Mode = GPIO_MODE_OUTPUT_PP;
	GPIO_InitStruct.Pull = GPIO_PULLUP;
	GPIO_InitStruct.Speed = GPIO_SPEED_FREQ_LOW;
	HAL_GPIO_Init(WIFI_EN_GPIO_Port, &GPIO_InitStruct);

	/*Configure GPIO pins : WIFI_TX_Pin WIFI_RX_Pin */
	GPIO_InitStruct.Pin = WIFI_TX_Pin | WIFI_RX_Pin;
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	GPIO_InitStruct.Alternate = GPIO_AF8_UART4;
	HAL_GPIO_Init(GPIOC, &GPIO_InitStruct);

	/*Configure GPIO pin : WIFI_RST_Pin */
	GPIO_InitStruct.Pin = WIFI_RST_Pin;
	GPIO_InitStruct.Mode = GPIO_MODE_OUTPUT_PP;
	GPIO_InitStruct.Pull = GPIO_PULLUP;
	GPIO_InitStruct.Speed = GPIO_SPEED_FREQ_LOW;
	HAL_GPIO_Init(WIFI_RST_GPIO_Port, &GPIO_InitStruct);

	/*Configure GPIO pin : LED_BUILTIN_Pin */
	GPIO_InitStruct.Pin = LED_BUILTIN_Pin;
	GPIO_InitStruct.Mode = GPIO_MODE_OUTPUT_PP;
	GPIO_InitStruct.Pull = GPIO_PULLUP;
	GPIO_InitStruct.Speed = GPIO_SPEED_FREQ_LOW;
	HAL_GPIO_Init(LED_BUILTIN_GPIO_Port, &GPIO_InitStruct);

}

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
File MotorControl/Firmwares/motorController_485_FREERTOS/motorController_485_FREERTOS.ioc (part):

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Mcu.Name=STM32F103C(8-B)Tx
Mcu.Package=LQFP48
Mcu.UserName=STM32F103C8Tx
PA1.GPIOParameters=GPIO_PuPd,GPIO_Label,GPIO_ModeDefaultEXTI
PA1.GPIO_Label=MTR_AZ_ZERO
PA1.GPIO_ModeDefaultEXTI=GPIO_MODE_IT_FALLING
PA1.GPIO_PuPd=GPIO_PULLUP
PA1.Signal=GPXTI1
PA10.GPIOParameters=GPIO_PuPd,GPIO_Label,GPIO_ModeDefaultEXTI
PA10.GPIO_Label=COCK_ALM
PA10.GPIO_ModeDefaultEXTI=GPIO_MODE_IT_FALLING
PA10.GPIO_PuPd=GPIO_PULLUP
PA10.Signal=GPXTI10
PA11.GPIOParameters=GPIO_PuPd,GPIO_Label
PA11.GPIO_Label=BUS_RXD
PA11.GPIO_PuPd=GPIO_PULLUP
PA11.Mode=Master
PA11.Signal=CAN_RX
PA12.GPIOParameters=GPIO_Label
PA12.GPIO_Label=BUS_TXD
PA12.Mode=Master
PA12.Signal=CAN_TX
PA13.Mode=Serial_Wire
PA13.Signal=SYS_JTMS-SWDIO
PA14.Mode=Serial_Wire
PA14.Signal=SYS_JTCK-SWCLK
PA2.GPIOParameters=GPIO_Label
PA2.GPIO_Label=MTR_AZ_TXD
PA2.Mode=Asynchronous
PA2.Signal=USART2_TX
PA3.GPIOParameters=GPIO_Label
PA3.GPIO_Label=MTR_AZ_RXD
PA3.Mode=Asynchronous
PA3.Signal=USART2_RX
PA6.GPIOParameters=GPIO_Speed,GPIO_Label
PA6.GPIO_Label=TRIGGER_ENABLE
PA6.GPIO_Speed=GPIO_SPEED_FREQ_HIGH
PA6.Signal=S_TIM3_CH1
PA8.GPIOParameters=GPIO_Speed,GPIO_Label
PA8.GPIO_Label=COCK_DIR
PA8.GPIO_Speed=GPIO_SPEED_FREQ_HIGH
PA8.Signal=S_TIM1_CH1
PA9.GPIOParameters=GPIO_Speed,GPIO_Label
PA9.GPIO_Label=COCK_PLS
PA9.GPIO_Speed=GPIO_SPEED_FREQ_HIGH
PA9.Signal=S_TIM1_CH2
PB0.GPIOParameters=GPIO_Label
PB0.GPIO_Label=COCK_POS
PB0.Signal=ADCx_IN8
PB1.GPIOParameters=GPIO_Speed,GPIO_Label
PB1.GPIO_Label=LED_BUILTIN
PB1.GPIO_Speed=GPIO_SPEED_FREQ_MEDIUM
PB1.Signal=S_TIM3_CH4
PB10.GPIOParameters=GPIO_Label
PB10.GPIO_Label=MTR_EL_TXD
PB10.Mode=Asynchronous
PB10.Signal=USART3_TX
PB11.GPIOParameters=GPIO_Label
PB11.GPIO_Label=MTR_EL_RXD
PB11.Mode=Asynchronous
PB11.Signal=USART3_RX
PB15.GPIOParameters=GPIO_Speed,GPIO_PuPd,GPIO_Label
PB15.GPIO_Label=COCK_AWO
PB15.GPIO_PuPd=GPIO_PULLUP
PB15.GPIO_Speed=GPIO_SPEED_FREQ_MEDIUM
PB15.Signal=GPIO_Output
PB2.GPIOParameters=GPIO_PuPd,GPIO_Label,GPIO_ModeDefaultEXTI
PB2.GPIO_Label=MTR_EL_ZERO
PB2.GPIO_ModeDefaultEXTI=GPIO_MODE_IT_FALLING
PB2.GPIO_PuPd=GPIO_PULLUP
PB2.Signal=GPXTI2
PD0-OSC_IN.Mode=HSE-External-Oscillator
PD0-OSC_IN.Signal=RCC_OSC_IN
PD1-OSC_OUT.Mode=HSE-External-Oscillator
PD1-OSC_OUT.Signal=RCC_OSC_OUT
RCC.SYSCLKFreq_VALUE=72000000
RCC.SYSCLKSource=RCC_SYSCLKSOURCE_PLLCLK
board=custom

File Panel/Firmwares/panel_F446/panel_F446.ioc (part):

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Mcu.Name=STM32F446R(C-E)Tx
Mcu.Package=LQFP64
Mcu.UserName=STM32F446RETx
PA10.GPIOParameters=GPIO_PuPd,GPIO_Label
PA10.GPIO_Label=PC_RX
PA10.GPIO_PuPd=GPIO_PULLUP
PA10.Mode=Asynchronous
PA10.Signal=USART1_RX
PA11.GPIOParameters=GPIO_Label
PA11.GPIO_Label=BUS_RX
PA11.Mode=CAN_Activate
PA11.Signal=CAN1_RX
PA12.GPIOParameters=GPIO_Label
PA12.GPIO_Label=BUS_TX
PA12.Mode=CAN_Activate
PA12.Signal=CAN1_TX
PA13.GPIOParameters=GPIO_Label
PA13.GPIO_Label=TMS
PA13.Mode=Serial_Wire
PA13.Signal=SYS_JTMS-SWDIO
PA14.GPIOParameters=GPIO_Label
PA14.GPIO_Label=TCK
PA14.Mode=Serial_Wire
PA14.Signal=SYS_JTCK-SWCLK
PA15.GPIOParameters=GPIO_PuPd,GPIO_Label
PA15.GPIO_Label=WIFI_EN
PA15.GPIO_PuPd=GPIO_PULLUP
PA15.Signal=GPIO_Output
PA2.GPIOParameters=GPIO_Label
PA2.GPIO_Label=DEBUG_TX
PA2.Mode=Asynchronous
PA2.Signal=USART2_TX
PA3.GPIOParameters=GPIO_PuPd,GPIO_Label
PA3.GPIO_Label=DEBUG_RX
PA3.GPIO_PuPd=GPIO_PULLUP
PA3.Mode=Asynchronous
PA3.Signal=USART2_RX
PA7.GPIOParameters=GPIO_Label
PA7.GPIO_Label=BATT_VOLT
PA7.Signal=ADCx_IN7
PA9.GPIOParameters=GPIO_Label
PA9.GPIO_Label=PC_TX
PA9.Mode=Asynchronous
PA9.Signal=USART1_TX
PB10.GPIOParameters=GPIO_Label
PB10.GPIO_Label=BUTTON_TX
PB10.Mode=Asynchronous
PB10.Signal=USART3_TX
PB12.GPIOParameters=GPIO_PuPd,GPIO_Label
PB12.GPIO_Label=TRIGGER_IN
PB12.GPIO_PuPd=GPIO_PULLUP
PB12.Signal=GPIO_Input
PB15.GPIOParameters=GPIO_Speed,GPIO_PuPd,GPIO_Label
PB15.GPIO_Label=TRIG_PULSE_OUT
PB15.GPIO_PuPd=GPIO_PULLDOWN
PB15.GPIO_Speed=GPIO_SPEED_FREQ_VERY_HIGH
PB15.Signal=S_TIM12_CH2
PC10.GPIOParameters=GPIO_Label
PC10.GPIO_Label=WIFI_TX
PC10.Signal=UART4_TX
PC11.GPIOParameters=GPIO_Label
PC11.GPIO_Label=WIFI_RX
PC11.Signal=UART4_RX
PC12.GPIOParameters=GPIO_PuPd,GPIO_Label
PC12.GPIO_Label=WIFI_RST
PC12.GPIO_PuPd=GPIO_PULLUP
PC12.Signal=GPIO_Output
PC5.GPIOParameters=GPIO_PuPd,GPIO_Label
PC5.GPIO_Label=BUTTON_RX
PC5.GPIO_PuPd=GPIO_PULLUP
PC5.Mode=Asynchronous
PC5.Signal=USART3_RX
PC6.GPIOParameters=GPIO_Label
PC6.GPIO_Label=STAB_TX
PC6.Mode=Asynchronous
PC6.Signal=USART6_TX
PC7.GPIOParameters=GPIO_PuPd,GPIO_Label
PC7.GPIO_Label=STAB_RX
PC7.GPIO_PuPd=GPIO_PULLUP
PC7.Mode=Asynchronous
PC7.Signal=USART6_RX
PC8.GPIOParameters=GPIO_PuPd,GPIO_Label
PC8.GPIO_Label=PC_PWR_CHECK_IN
PC8.GPIO_PuPd=GPIO_PULLUP
PC8.Signal=GPIO_Input
PC9.GPIOParameters=GPIO_PuPd,GPIO_Label
PC9.GPIO_Label=PC_IGNITION
PC9.GPIO_PuPd=GPIO_PULLDOWN
PC9.Signal=GPIO_Output
PD2.GPIOParameters=PinState,GPIO_PuPd,GPIO_Label
PD2.GPIO_Label=LED_BUILTIN
PD2.GPIO_PuPd=GPIO_PULLUP
PD2.PinState=GPIO_PIN_RESET
PD2.Signal=GPIO_Output
PH0-OSC_IN.Mode=HSE-External-Oscillator
PH0-OSC_IN.Signal=RCC_OSC_IN
PH1-OSC_OUT.Mode=HSE-External-Oscillator
PH1-OSC_OUT.Signal=RCC_OSC_OUT
RCC.HSE_VALUE=8000000
RCC.SYSCLKFreq_VALUE=180000000
RCC.SYSCLKSource=RCC_SYSCLKSOURCE_PLLCLK
board=NUCLEO-F446RE
boardIOC=true

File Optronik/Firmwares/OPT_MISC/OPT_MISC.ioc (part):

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Mcu.Name=STM32F103C(8-B)Tx
Mcu.Package=LQFP48
Mcu.UserName=STM32F103C8Tx
PA10.GPIOParameters=GPIO_Label
PA10.GPIO_Label=LRF_TXD
PA10.Mode=Asynchronous
PA10.Signal=USART1_RX
PA11.GPIOParameters=GPIO_Label
PA11.GPIO_Label=BUS_RXD
PA11.Mode=Master
PA11.Signal=CAN_RX
PA12.GPIOParameters=GPIO_Label
PA12.GPIO_Label=BUS_TXD
PA12.Mode=Master
PA12.Signal=CAN_TX
PA13.Mode=Serial_Wire
PA13.Signal=SYS_JTMS-SWDIO
PA14.Mode=Serial_Wire
PA14.Signal=SYS_JTCK-SWCLK
PA2.GPIOParameters=GPIO_Label
PA2.GPIO_Label=IMU_RXD
PA2.Mode=Asynchronous
PA2.Signal=USART2_TX
PA3.GPIOParameters=GPIO_Label
PA3.GPIO_Label=IMU_TXD
PA3.Mode=Asynchronous
PA3.Signal=USART2_RX
PA8.Mode=Clock-out
PA8.Signal=RCC_MCO
PA9.GPIOParameters=GPIO_Label
PA9.GPIO_Label=LRF_RXD
PA9.Mode=Asynchronous
PA9.Signal=USART1_TX
PB10.GPIOParameters=GPIO_Label
PB10.GPIO_Label=GPS_RXD
PB10.Mode=Asynchronous
PB10.Signal=USART3_TX
PB11.GPIOParameters=GPIO_Label
PB11.GPIO_Label=GPS_TXD
PB11.Mode=Asynchronous
PB11.Signal=USART3_RX
PC13-TAMPER-RTC.GPIOParameters=GPIO_Speed,PinState,GPIO_PuPd,GPIO_Label,GPIO_ModeDefaultOutputPP
PC13-TAMPER-RTC.GPIO_Label=LRF_EN
PC13-TAMPER-RTC.GPIO_ModeDefaultOutputPP=GPIO_MODE_OUTPUT_OD
PC13-TAMPER-RTC.GPIO_PuPd=GPIO_NOPULL
PC13-TAMPER-RTC.GPIO_Speed=GPIO_SPEED_FREQ_MEDIUM
PC13-TAMPER-RTC.PinState=GPIO_PIN_SET
PC13-TAMPER-RTC.Signal=GPIO_Output
PD0-OSC_IN.Mode=HSE-External-Oscillator
PD0-OSC_IN.Signal=RCC_OSC_IN
PD1-OSC_OUT.Mode=HSE-External-Oscillator
PD1-OSC_OUT.Signal=RCC_OSC_OUT
RCC.SYSCLKFreq_VALUE=72000000
RCC.SYSCLKSource=RCC_SYSCLKSOURCE_PLLCLK
board=custom

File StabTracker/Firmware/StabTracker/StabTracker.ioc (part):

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Mcu.Name=STM32F446R(C-E)Tx
Mcu.Package=LQFP64
Mcu.UserName=STM32F446RETx
PA10.GPIOParameters=GPIO_PuPd,GPIO_Label
PA10.GPIO_Label=IMU_RX
PA10.GPIO_PuPd=GPIO_PULLUP
PA10.Mode=Asynchronous
PA10.Signal=USART1_RX
PA11.GPIOParameters=GPIO_PuPd,GPIO_Label
PA11.GPIO_Label=BUS_RX
PA11.GPIO_PuPd=GPIO_PULLUP
PA11.Mode=CAN_Activate
PA11.Signal=CAN1_RX
PA12.GPIOParameters=GPIO_PuPd,GPIO_Label
PA12.GPIO_Label=BUS_TX
PA12.GPIO_PuPd=GPIO_PULLUP
PA12.Mode=CAN_Activate
PA12.Signal=CAN1_TX
PA13.GPIOParameters=GPIO_Label
PA13.GPIO_Label=TMS
PA13.Mode=Serial_Wire
PA13.Signal=SYS_JTMS-SWDIO
PA14.GPIOParameters=GPIO_Label
PA14.GPIO_Label=TCK
PA14.Mode=Serial_Wire
PA14.Signal=SYS_JTCK-SWCLK
PA2.GPIOParameters=GPIO_Label
PA2.GPIO_Label=DEBUG_TX
PA2.Mode=Asynchronous
PA2.Signal=USART2_TX
PA3.GPIOParameters=GPIO_PuPd,GPIO_Label
PA3.GPIO_Label=DEBUG_RX
PA3.GPIO_PuPd=GPIO_PULLUP
PA3.Mode=Asynchronous
PA3.Signal=USART2_RX
PA5.GPIOParameters=GPIO_Label
PA5.GPIO_Label=LED_BUILTIN
PA5.Signal=S_TIM2_CH1_ETR
PA9.GPIOParameters=GPIO_Label
PA9.GPIO_Label=IMU_TX
PA9.Mode=Asynchronous
PA9.Signal=USART1_TX
PH0-OSC_IN.Mode=HSE-External-Oscillator
PH0-OSC_IN.Signal=RCC_OSC_IN
PH1-OSC_OUT.Mode=HSE-External-Oscillator
PH1-OSC_OUT.Signal=RCC_OSC_OUT
RCC.HSE_VALUE=8000000
RCC.SYSCLKFreq_VALUE=180000000
RCC.SYSCLKSource=RCC_SYSCLKSOURCE_PLLCLK
board=NUCLEO-F446RE
boardIOC=true

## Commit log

2018-11-19 v2.0.0
    Firmware's Skeleton for:
    1. MotorControl
    2. Optronik:
    a. OPT_CAM
    b. OPT_MISC
2020-02-27 v2.1.0
2020-07-08 remove motorController
2020-07-08 add new motorController skeleton
2020-07-14 motorController using CAN done
    maximal speed at 1700RPM -> 115000 c/s
2021-02-02 implement stabilized module
    changelog:
    1. add stabilized module
    2. output angle & angular velocity to can bus
    3. change motor command rate to 100Hz
    4. change tracking control function
2021-02-04 tracker logger added
2021-02-04 change data rate to 200Hz
    Changelog:
    1. change CAN bus baud rate to 500kbps
    2. change motor data rate to 200Hz
2021-02-09 add stabilize algorithm to motorController
    changelog:
    - add stab algorithm to motorController
    - stabilized module change to imu module
    - imu module sending 200Hz pitch roll when stab ON
    - imu sending YPR in 10Hz
    - panel sending stab correction speed
2021-02-09 Revert "add stabilize algorithm to motorController"
    This reverts commit cf9d517c3015458b58b7940c70b162da2cd40f1b.
2021-02-10 change data rate to 100Hz
    changelog:
    - change data rate stabilize to 100Hz
    - data out stab module send directly to motorController
2021-02-10 add stabControl to motorControl
    changelog:
    - add skeleton (unfinished)
2021-02-10 Revert "add stabControl to motorControl"
    This reverts commit cba918d5b6c0c59a66daf927579500fcb2686614.
2021-02-10 Revert "change data rate to 100Hz"
    This reverts commit dab9432a420b981d945815ab0da7c72165903b25.
2021-02-10 Revert "Revert "change data rate to 100Hz""
    This reverts commit 9acc7dfb9b0539415d1886535320aa56c5047b3e.
2021-02-10 tidy up motorControl
2021-02-10 DEV-STAB temp
2021-02-10 Revert "DEV-STAB temp"
    This reverts commit a1c3928487bb0004f1b4590b5f40d119d2f211b3.
2021-02-10 Revert "tidy up motorControl"
    This reverts commit 811e48e1a20db5133546eff21529c18726f3974a.
2021-02-10 temp
2021-02-16 add stacker modul
    changelog:
    - add stabilizer & tracker module
    - put common library (rwsCanID.h, uart & servoDriver) to folder Documents\Library\
2021-02-16 change motor control algorithm-NOT DONE YET!
2021-02-16 change motor control algorithm
    ready to debug
2021-02-17 first test of new motor contol algorithm
2021-02-17 setting OK
2021-02-17 setting all main project OK
2021-02-17 DEBUG
2021-02-18 debug
    changelog:
    1. update tuning tracking
    2. add YPR platform
    3. change CAN_RECEIVE_TIMEOUT to 1s
    4. add zoomLevel 3 when thermal ON
2021-03-02 remove StabTracker Module
2021-03-08 Revert "remove StabTracker Module"
    This reverts commit c0d9053d518a0c03f946f8340bac436335de20cf.
2021-03-08 Revert "debug"
    This reverts commit f2047a51bf3c0c49d49e555a5bf724b488ac2f17.
2021-03-09 skeleton stacker on platform based on F446
